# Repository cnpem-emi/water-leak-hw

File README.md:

# Water leak detector
Leak sensor module, capacitance based.

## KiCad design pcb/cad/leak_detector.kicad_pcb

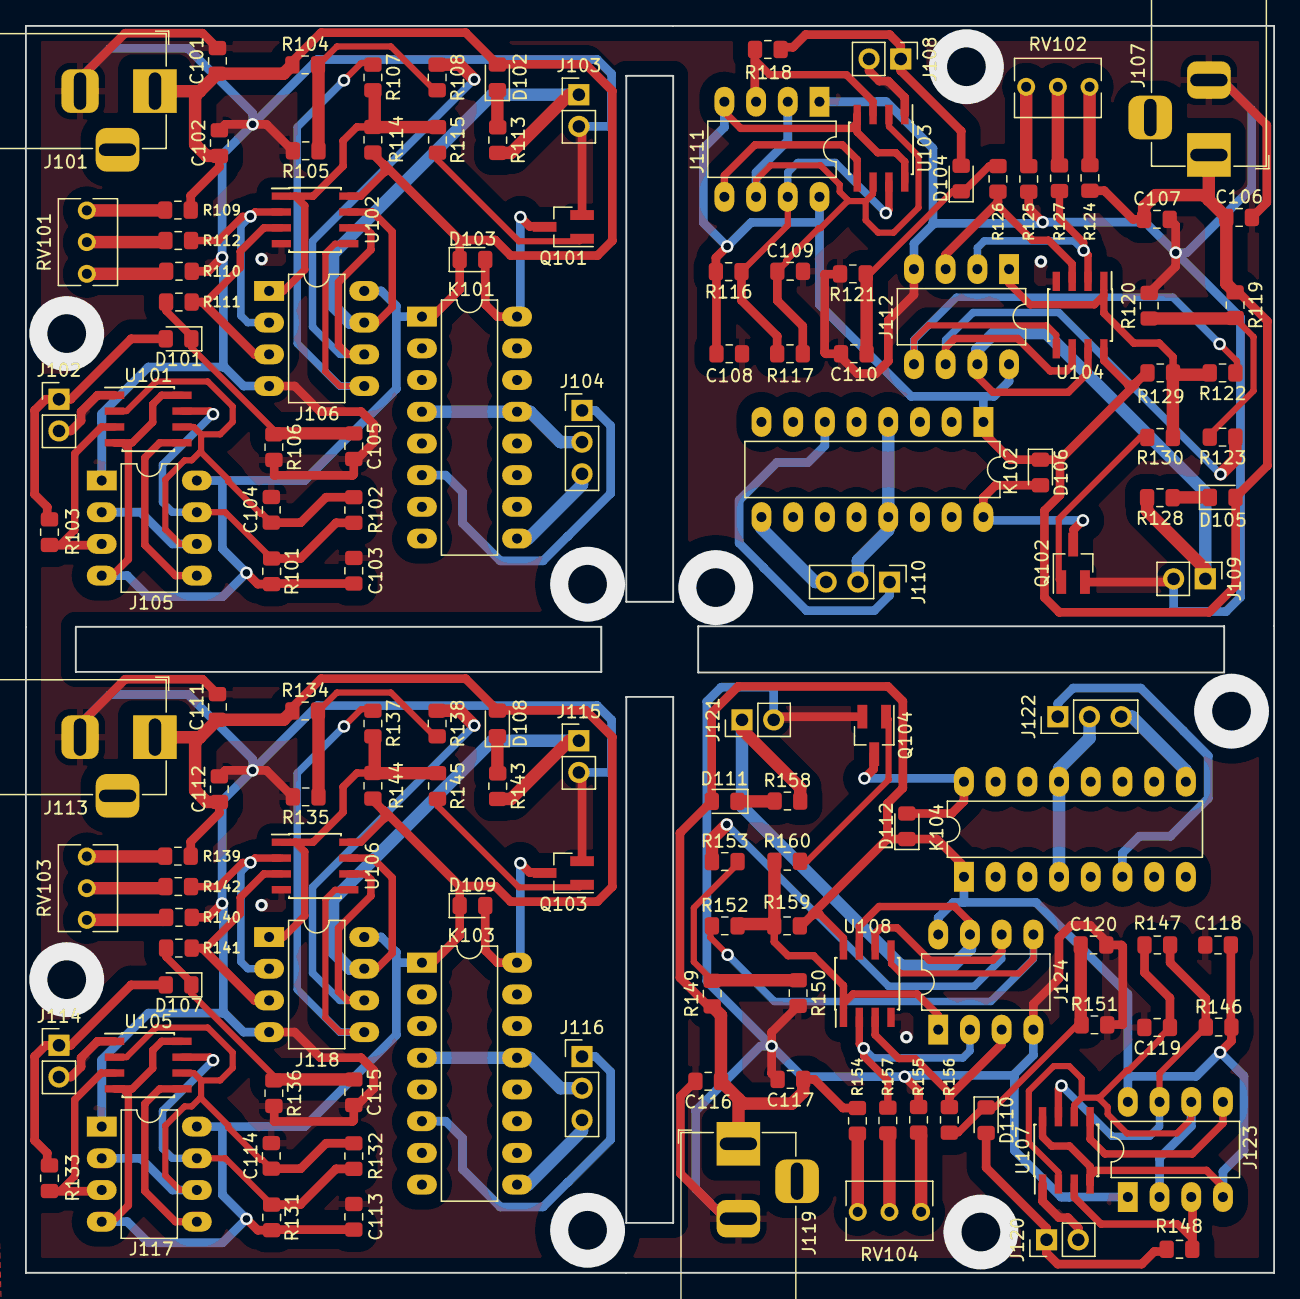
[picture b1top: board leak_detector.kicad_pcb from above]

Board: 2 copper layers, 100.0 x 99.9 mm, 136 parts (0 on the bottom side), 24 nets.

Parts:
C101, C106, C111, C116: 10u; C_0805_2012Metric_Pad1.15x1.40mm_HandSolder
C102, C103, C105, C107, C108, C110, C112, C113, C115, C117, C118, C120: 0.1u; C_0805_2012Metric_Pad1.15x1.40mm_HandSolder
C104, C109, C114, C119: 10n; C_0805_2012Metric_Pad1.15x1.40mm_HandSolder
D101, D103, D104, D106, D107, D109, D110, D112: 1n4148/1n914; D_0805_2012Metric_Pad1.15x1.40mm_HandSolder
D102, D105, D108, D111: LED; LED_0805_2012Metric_Pad1.15x1.40mm_HandSolder
J101, J107, J113, J119: Jack-DC; BarrelJack_Horizontal
J102, J103, J108, J109, J114, J115, J120, J121: Conn_01x02; PinHeader_1x02_P2.54mm_Vertical
J104, J110, J116, J122: Conn_01x03; PinHeader_1x03_P2.54mm_Vertical
J105, J111, J117, J123: 555_Dip; DIP-8_W7.62mm_LongPads
J106, J112, J118, J124: 393_Dip; DIP-8_W7.62mm_LongPads
K101, K102, K103, K104: G5V-2; DIP-16_W7.62mm_LongPads
Q101, Q102, Q103, Q104: BSR14; SOT-23_Handsoldering
R101, R116, R131, R146: 3k3; R_0805_2012Metric_Pad1.15x1.40mm_HandSolder
R102, R117, R132, R147: 1k5; R_0805_2012Metric_Pad1.15x1.40mm_HandSolder
R103, R118, R133, R148: 51k; R_0805_2012Metric_Pad1.15x1.40mm_HandSolder
R104, R105, R119, R120, R134, R135, R149, R150: 4k7; R_0805_2012Metric_Pad1.15x1.40mm_HandSolder
R106, R121, R136, R151: 100k; R_0805_2012Metric_Pad1.15x1.40mm_HandSolder
R107, R108, R111, R112, R115, R122, R123, R126, R127, R130, R137, R138, R141, R142, R145, R152, R153, R156, R157, R160: 10k; R_0805_2012Metric_Pad1.15x1.40mm_HandSolder
R109, R124, R139, R154: 470; R_0805_2012Metric_Pad1.15x1.40mm_HandSolder
R110, R125, R140, R155: 100; R_0805_2012Metric_Pad1.15x1.40mm_HandSolder
R113, R114, R128, R129, R143, R144, R158, R159: 1k; R_0805_2012Metric_Pad1.15x1.40mm_HandSolder
RV101, RV102, RV103, RV104: 5k; Potentiometer_Bourns_3266Y_Vertical
U101, U103, U105, U107: LM555; SOIC-8_3.9x4.9mm_P1.27mm
U102, U104, U106, U108: LM393; SOIC-8_3.9x4.9mm_P1.27mm

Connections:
+5V: C101.1, C102.1, C103.1, C106.1, C107.1, C108.1, C111.1, C112.1, C113.1, C116.1, C117.1, C118.1, D102.2 (A), D103.1 (K), D105.2 (A), D106.1 (K), D108.2 (A), D109.1 (K), D111.2 (A), D112.1 (K), J101.1, J105.4, J105.8, J106.8, J107.1, J111.4, J111.8, J112.8, J113.1, J117.4, J117.8, J118.8, J119.1, J123.4, J123.8, J124.8, K101.1, K102.1, K103.1, K104.1, R101.1, R104.1, R109.1, R114.1, R116.1, R119.1, R124.1, R129.1, R131.1, R134.1, R139.1, R144.1, R146.1, R149.1, R154.1, R159.1, U101.4 (R), U101.8 (VCC), U102.8 (V+), U103.4 (R), U103.8 (VCC), U104.8 (V+), U105.4 (R), U105.8 (VCC), U106.8 (V+), U107.4 (R), U107.8 (VCC), U108.8 (V+)
/393_1: J106.1, J112.1, J118.1, J124.1, R107.2, R114.2, R115.2, R122.2, R129.2, R130.2, R137.2, R144.2, R145.2, R152.2, R159.2, R160.2, U102.1, U104.1, U106.1, U108.1
/393_2: J106.2, J112.2, J118.2, J124.2, R112.1, R127.1, R142.1, R157.1, U102.2 (-), U104.2 (-), U106.2 (-), U108.2 (-)
/393_3: J106.3, J112.3, J118.3, J124.3, R111.1, R126.1, R141.1, R156.1, U102.3 (+), U104.3 (+), U106.3 (+), U108.3 (+)
/393_5: J106.5, J112.5, J118.5, J124.5, R107.1, R122.1, R137.1, R152.1, U102.5 (+), U104.5 (+), U106.5 (+), U108.5 (+)
/393_6: J106.6, J112.6, J118.6, J124.6, R108.1, R123.1, R138.1, R153.1, U102.6 (_), U104.6 (_), U106.6 (_), U108.6 (_)
/393_7: J103.1, J106.7, J109.1, J112.7, J115.1, J118.7, J121.1, J124.7, R113.2, R128.2, R143.2, R158.2, U102.7, U104.7, U106.7, U108.7
/555_2: C104.1, C109.1, C114.1, C119.1, J105.2, J105.6, J111.2, J111.6, J117.2, J117.6, J123.2, J123.6, R102.2, R117.2, R132.2, R147.2, U101.2 (TR), U101.6 (THR), U103.2 (TR), U103.6 (THR), U105.2 (TR), U105.6 (THR), U107.2 (TR), U107.6 (THR)
/555_3: J105.3, J111.3, J117.3, J123.3, R103.1, R118.1, R133.1, R148.1, U101.3 (Q), U103.3 (Q), U105.3 (Q), U107.3 (Q)
/555_5: J105.5, J111.5, J117.5, J123.5, U101.5 (CV), U103.5 (CV), U105.5 (CV), U107.5 (CV)
/555_7: J105.7, J111.7, J117.7, J123.7, R101.2, R102.1, R116.2, R117.1, R131.2, R132.1, R146.2, R147.1, U101.7 (DIS), U103.7 (DIS), U105.7 (DIS), U107.7 (DIS)
GND: C101.2, C102.2, C103.2, C104.2, C105.2, C106.2, C107.2, C108.2, C109.2, C110.2, C111.2, C112.2, C113.2, C114.2, C115.2, C116.2, C117.2, C118.2, C119.2, C120.2, J101.2, J102.2, J103.2, J105.1, J106.4, J107.2, J108.2, J109.2, J111.1, J112.4, J113.2, J114.2, J115.2, J117.1, J118.4, J119.2, J120.2, J121.2, J123.1, J124.4, Q101.2 (E), Q102.2 (E), Q103.2 (E), Q104.2 (E), R105.2, R106.2, R110.2, R120.2, R121.2, R125.2, R135.2, R136.2, R140.2, R150.2, R151.2, R155.2, U101.1 (GND), U102.4 (V-), U103.1 (GND), U104.4 (V-), U105.1 (GND), U106.4 (V-), U107.1 (GND), U108.4 (V-)
unnamed: C105.1, C110.1, C115.1, C120.1, D101.1 (K), D104.1 (K), D107.1 (K), D110.1 (K), R106.1, R111.2, R121.1, R126.2, R136.1, R141.2, R151.1, R156.2
unnamed: D101.2 (A), D104.2 (A), D107.2 (A), D110.2 (A), J102.1, J108.1, J114.1, J120.1, R103.2, R118.2, R133.2, R148.2
unnamed: D102.1 (K), D105.1 (K), D108.1 (K), D111.1 (K), R113.1, R128.1, R143.1, R158.1
unnamed: D103.2 (A), D106.2 (A), D109.2 (A), D112.2 (A), K101.16, K102.16, K103.16, K104.16, Q101.3 (C), Q102.3 (C), Q103.3 (C), Q104.3 (C)
unnamed: J104.1, J110.1, J116.1, J122.1, K101.6, K102.6, K103.6, K104.6
unnamed: J104.2, J110.2, J116.2, J122.2, K101.4, K101.13, K102.4, K102.13, K103.4, K103.13, K104.4, K104.13
unnamed: J104.3, J110.3, J116.3, J122.3, K101.9, K102.9, K103.9, K104.9
unnamed: Q101.1 (B), Q102.1 (B), Q103.1 (B), Q104.1 (B), R115.1, R130.1, R145.1, R160.1
unnamed: R104.2, R105.1, R108.2, R119.2, R120.1, R123.2, R134.2, R135.1, R138.2, R149.2, R150.1, R153.2
unnamed: R109.2, R124.2, R139.2, R154.2, RV101.1, RV102.1, RV103.1, RV104.1
unnamed: R110.1, R125.1, R140.1, R155.1, RV101.3, RV102.3, RV103.3, RV104.3
unnamed: R112.2, R127.2, R142.2, R157.2, RV101.2, RV102.2, RV103.2, RV104.2

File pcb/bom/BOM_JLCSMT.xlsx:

Comment | Designator | Footprint | JLCPCB Part #（optional）
10u | C101,C106,C111,C116 | C_0805_2012Metric_Pad1.15x1.40mm_HandSolder | C105505
0.1u | C102,C103,C105,C113,C117,C120,C118,C108,C115,C110,C112,C107 | C_0805_2012Metric_Pad1.15x1.40mm_HandSolder | C29926
10n | C104,C119,C114,C109 | C_0805_2012Metric_Pad1.15x1.40mm_HandSolder | C83170
1n4148/1n914 | D101,D103,D106,D104,D107,D109,D112,D110 | D_0805_2012Metric_Pad1.15x1.40mm_HandSolder | C57759
LED | D102,D108,D111,D105 | LED_0805_2012Metric_Pad1.15x1.40mm_HandSolder | C601670
3k3 | R101,R146,R116,R131 | R_0805_2012Metric_Pad1.15x1.40mm_HandSolder | C114222
1k5 | R102,R117,R147,R132 | R_0805_2012Metric_Pad1.15x1.40mm_HandSolder | C114555
51k | R103,R118,R148,R133 | R_0805_2012Metric_Pad1.15x1.40mm_HandSolder | C17737
4k7 | R104,R105,R134,R119,R120,R149,R150,R135 | R_0805_2012Metric_Pad1.15x1.40mm_HandSolder | C229219
100k | R106,R121,R136,R151 | R_0805_2012Metric_Pad1.15x1.40mm_HandSolder | C149504
10k | R107,R108,R111,R112,R115,R122,R123,R157,R153,R137,R127,R138,R156,R145,R141,R142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 | R_0805_2012Metric_Pad1.15x1.40mm_HandSolder | C17414
470 | R109,R124,R154,R139 | R_0805_2012Metric_Pad1.15x1.40mm_HandSolder | C17710
100 | R110,R155,R140,R125 | R_0805_2012Metric_Pad1.15x1.40mm_HandSolder | C17408
1k | R113,R114,R159,R143,R144,R129,R128,R158 | R_0805_2012Metric_Pad1.15x1.40mm_HandSolder | C328437
LM555 | U101,U105,U107,U103 | SOIC-8_3.9x4.9mm_P1.27mm | C5125085
LM393 | U102,U108,U104,U106 | SOIC-8_3.9x4.9mm_P1.27mm | C400839
BSR14 | Q101,Q104,Q102,Q103 | SOT-23_Handsoldering | C713676

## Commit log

2023-04-04 Files added
